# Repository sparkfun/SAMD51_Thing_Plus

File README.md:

SparkFun SAMD51 Thing Plus
========================================

[*SparkFun SAMD51 Thing Plus (DEV-14713)*](https://www.sparkfun.com/products/14713)

With a 32-bit ARM Cortex-M4F MCU, the [SAMD51 Thing Plus](https://www.sparkfun.com/products/14713) is one of our most powerful microcontroller boards yet! The SAMD51 Thing Plus provides you with an economical and easy to use development platform if you're needing more power with minimal working space. This Thing even comes flashed with the same convenient UF2 bootloader as the RedBoard Turbo. To make the Thing Plus even easier to use, we've moved a few pins around to make the board Feather compatible and it utilizes our handy Qwiic Connect System which means no soldering or shields are required to connect it to the rest of your system!

The ATSAMD51J20 utilizes a 32-bit ARM Cortex-M4 processor with Floating Point Unit (FPU), running up to 120MHz, up to 1MB of flash memory, up to 256KB of SRAM with ECC, up to 6 SERCOM interfaces, and other features. In addition to the USB interface and Qwiic connection, a The SAMD51 Thing Plus provides a 600mA 3.3V regulator and LiPo charger.

Repository Contents
-------------------

* **/Documentation** - Documentation (datasheet, graphical datasheet, etc.)
* **/Hardware** - Eagle design files (.brd, .sch)
* **/Production** - Production panel files (.brd)

Documentation
--------------
* [**Hookup Guide**](https://learn.sparkfun.com/tutorials/samd51-thing-plus-hookup-guide) - Basic hookup guide for the SAMD51 Thing Plus.
* [**SAMD51 Datasheet**](https://github.com/sparkfun/SAMD51_Thing_Plus/blob/master/Documents/SAMD51_datasheet.pdf)- Datasheet for the SAMD51 chip.
* [**Graphical Datasheet**](https://github.com/sparkfun/SAMD51_Thing_Plus/blob/master/Documents/SAMD51_Thing_Plus_graphical_datasheet_v01-02.pdf)- Graphical datasheet for the SAMD51 Thing Plus.

Product Versions
----------------
* [DEV-14713](https://www.sparkfun.com/products/14713) - Initial release of the SAMD51 Thing Plus.

Version History
---------------
* [V_1.0](https://github.com/sparkfun/SAMD51_Thing_Plus/releases/tag/v1.0.0) - Initial release of the SAMD51 Thing Plus.

License Information
-------------------

This product is _**open source**_! 

Please review the LICENSE.md file for license information.

If you have any questions or concerns on licensing, please visit the [SparkFun Forum](https://forum.sparkfun.com/index.php) and post a topic.

Distributed as-is; no warranty is given.

- Your friends at SparkFun.

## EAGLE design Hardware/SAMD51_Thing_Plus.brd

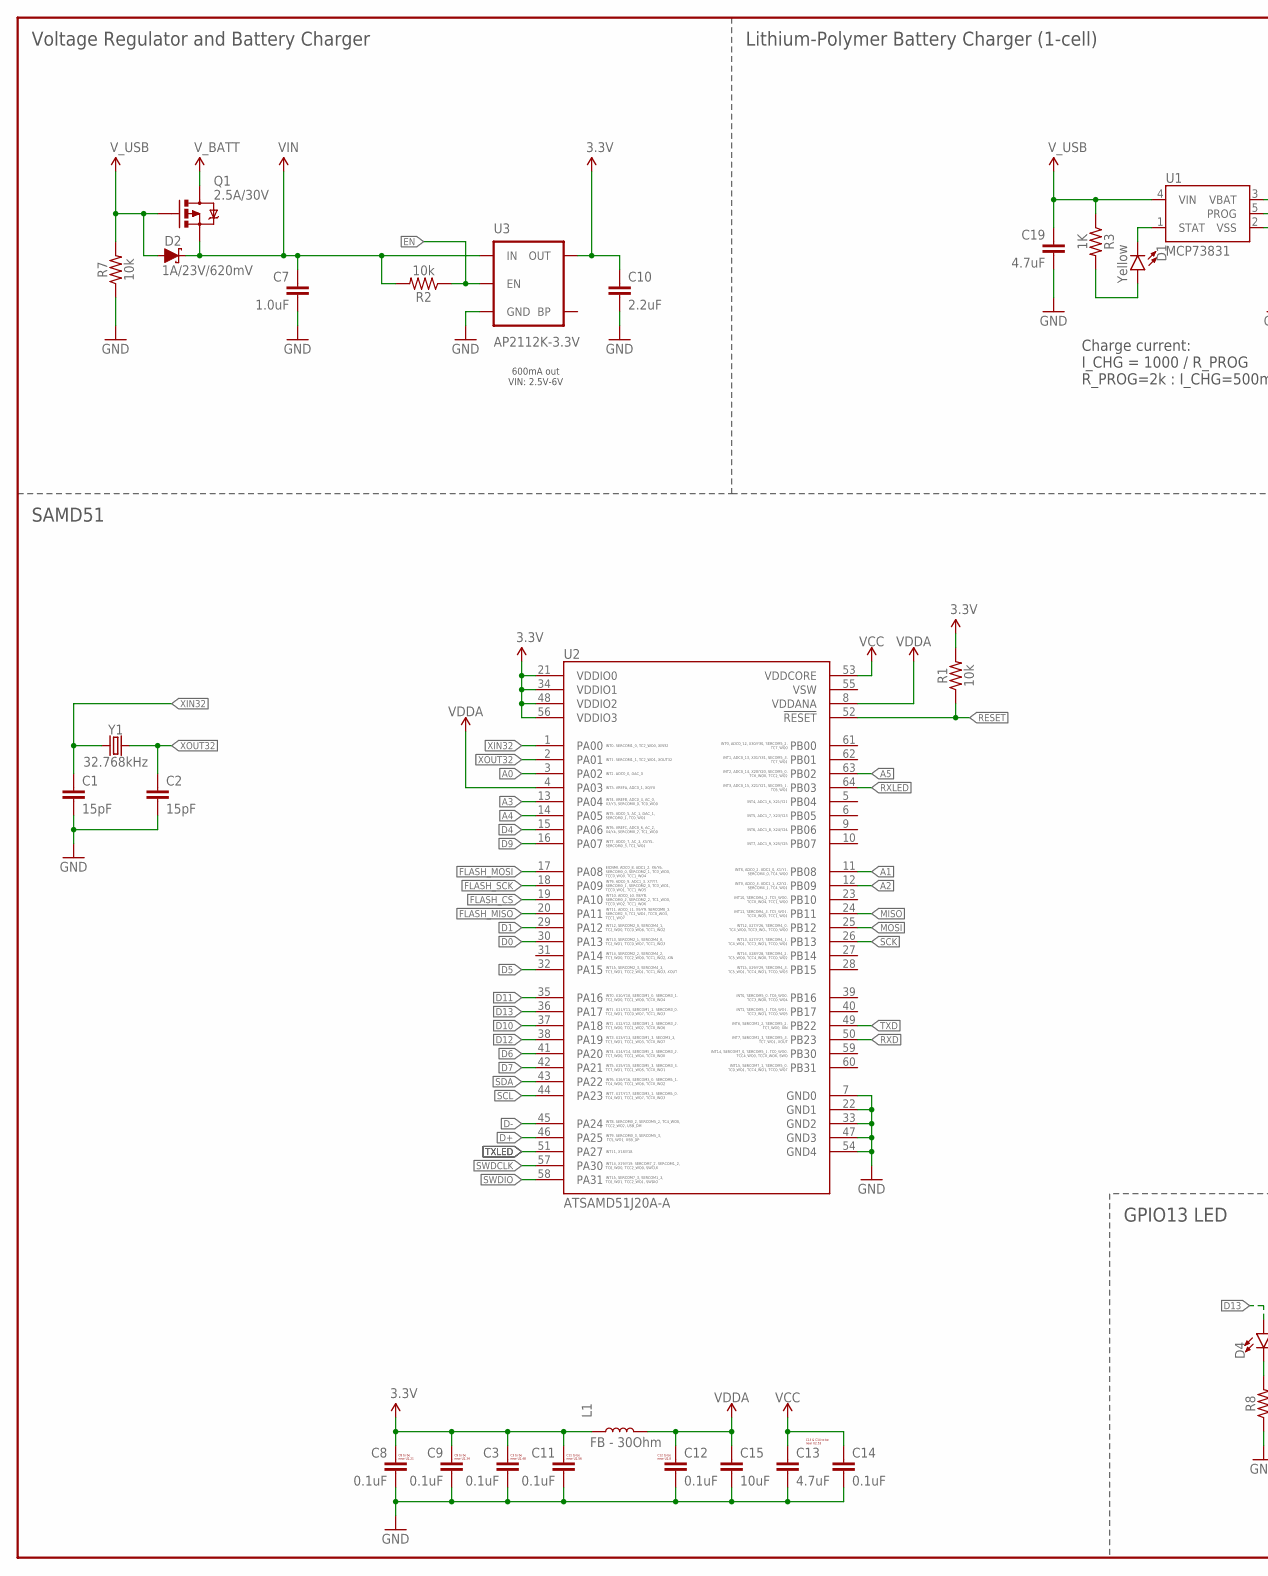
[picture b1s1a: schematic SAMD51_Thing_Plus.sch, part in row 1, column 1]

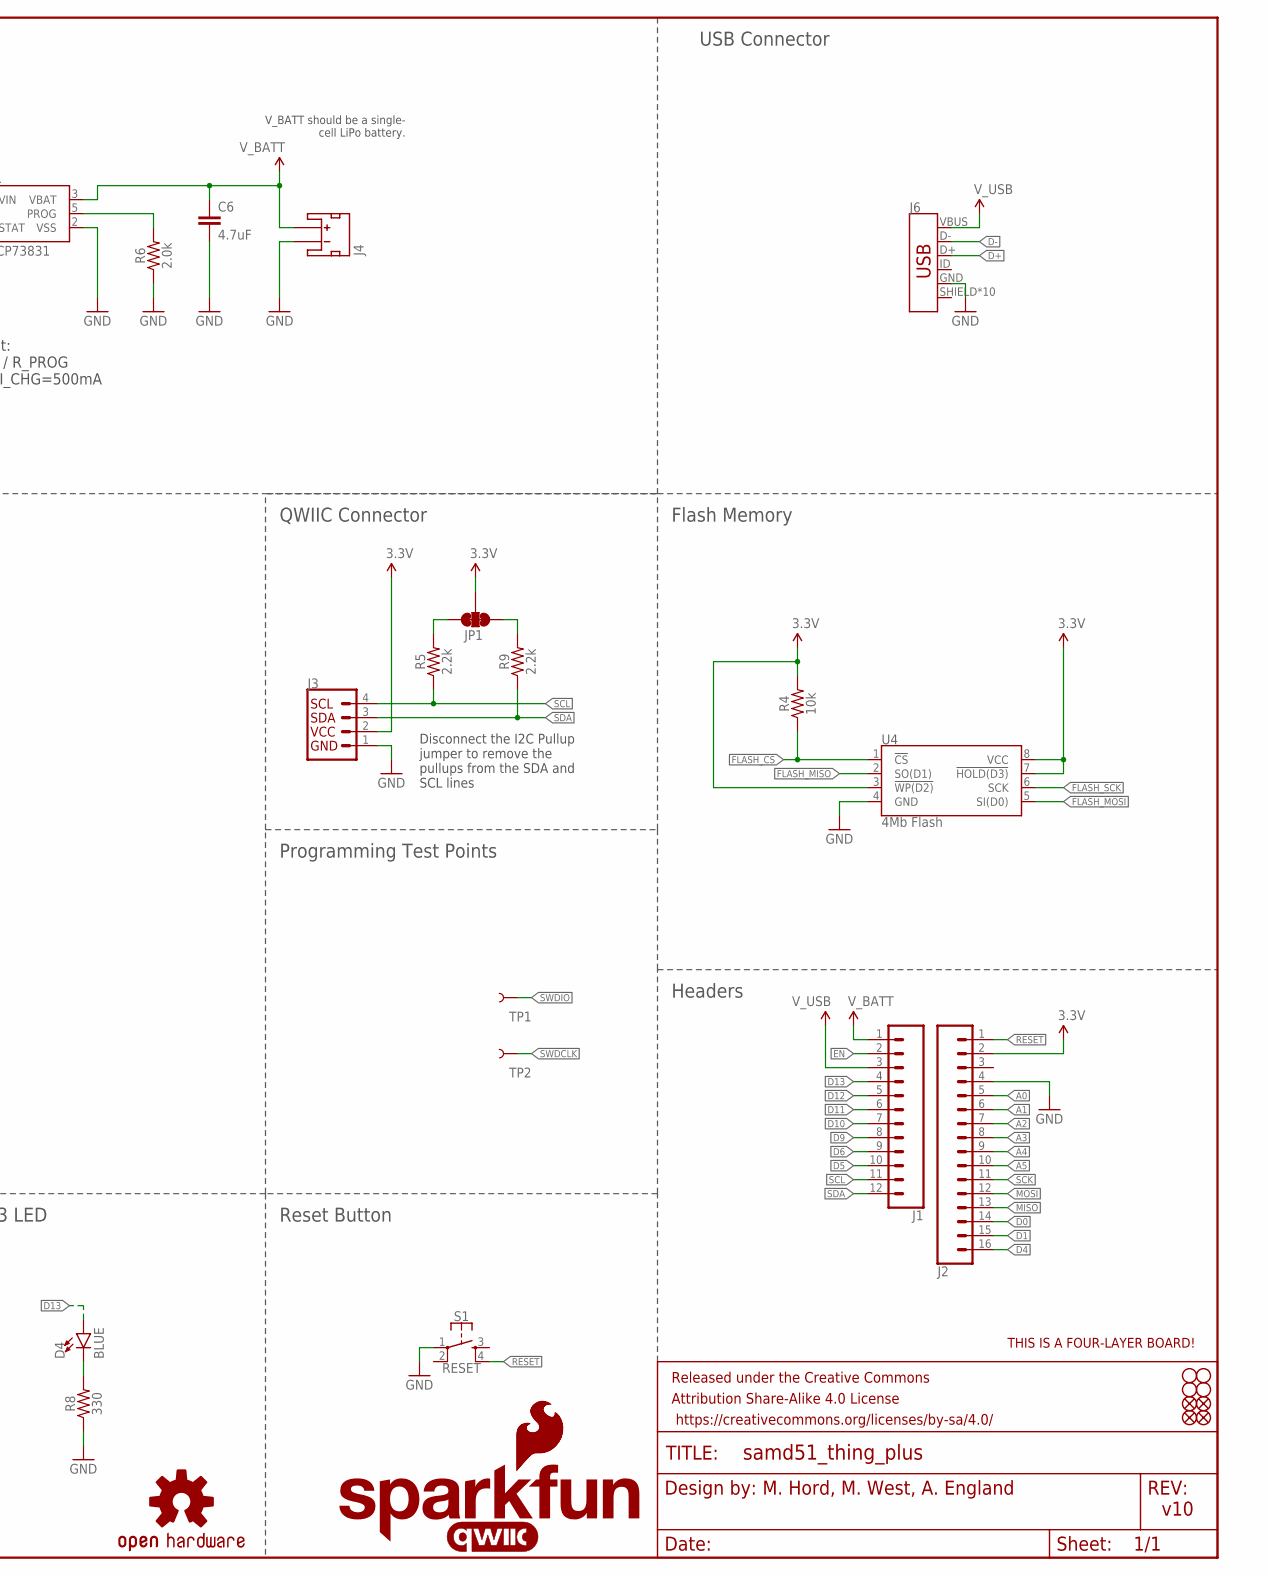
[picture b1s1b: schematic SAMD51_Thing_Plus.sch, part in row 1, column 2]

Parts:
C1, C2: 15pF; 0402
C3, C8, C9, C11, C12, C14: 0.1uF; 0402
C6, C13, C19: 4.7uF; 0603
C7: 1.0uF; 0603
C10: 2.2uF; 0603
C15: 10uF; 0805
D1: Yellow; LED-0603
D2: 1A/23V/620mV; SOD-323
D4: BLUE; LED-0603
FD1, FD2, FD3, FD4: FIDUCIALUFIDUCIAL; FIDUCIAL-MICRO
FRAME1: FRAME-LEDGER; CREATIVE_COMMONS
H1, H2, H3, H4: STAND-OFF
J1: CONN_12SM_SQ_NO_SILK; 1X12_SM_SQ_NOSILK
J2: CONN_161X16_SM_SQ_NOSILK; 1X16_SM_SQ_NOSILK
J3: QWIIC_CONNECTORJS-1MM; JST04_1MM_RA
J4: JST_2MM_MALE; JST-2-SMD
J6: AMP FCI 10103594-0001LF; USB-MICROB-PTH-MILL
JP1: JUMPER-SMT_3_2-NC_TRACE_SILK; SMT-JUMPER_3_2-NC_TRACE_SILK
L1: FB - 30Ohm; 0603
LOGO1: FOUR_LAYER_WARNING
LOGO2: OSHW-LOGOMINI; OSHW-LOGO-MINI
LOGO3: SFE_LOGO_NAME_FLAME.1_INCH; SFE_LOGO_NAME_FLAME_.1
LOGO4: SFE_LOGO_FLAME.1_INCH; SFE_LOGO_FLAME_.1
Q1: 2.5A/30V; SOT23-3@1
R1, R2, R4, R7: 10k; 0603
R3: 1K; 0603
R5, R9: 2.2k; 0603
R6: 2.0k; 0603
R8: 330; 0603
S1: RESET; TACTILE_SWITCH_SMD_4.6X2.8MM
TP1, TP2: TEST-POINTTP_15TH_THRU; TP_15TH
U1: MCP73831; SOT23-5
U2: ATSAMD51J20A-A; TQFP64
U3: AP2112K-3.3V; SOT23-5
U4: 4Mb Flash; SO08
U$69: QWIIC_LOGO_5MM; QWIIC_5MM
Y1: 32.768kHz; CRYSTAL-SMD-3.2X1.5MM

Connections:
3.3V: C3.1, C8.1, C9.1, C10.1, C11.1, J2.2, J3.2, JP1.2, L1.1, R1.2, R4.2, U2.21 (VDDIO0), U2.34 (VDDIO1), U2.48 (VDDIO2), U2.56 (VDDIO3), U3.5 (OUT), U4.3 (!WP(D2)), U4.7 (!HOLD(D3)), U4.8 (VCC)
!RESET: J2.1, R1.1, S1.4, U2.52 (!RESET)
A0: J2.5, U2.3 (PA02)
A1: J2.6, U2.11 (PB08)
A2: J2.7, U2.12 (PB09)
A3: J2.8, U2.13 (PA04)
A4: J2.9, U2.14 (PA05)
A5: J2.10, U2.63 (PB02)
D0: J2.14, U2.30 (PA13)
D1: J2.15, U2.29 (PA12)
D4: J2.16, U2.15 (PA06)
D5: J1.10, U2.32 (PA15)
D6: J1.9, U2.41 (PA20)
D7: U2.42 (PA21)
D9: J1.8, U2.16 (PA07)
D10: J1.7, U2.37 (PA18)
D11: J1.6, U2.35 (PA16)
D12: J1.5, U2.38 (PA19)
D13: D4.A, J1.4, U2.36 (PA17)
D+: J6.D+, U2.46 (PA25)
D-: J6.D-, U2.45 (PA24)
EN: J1.2, R2.1, U3.3 (EN)
FLASH_CS: R4.1, U2.19 (PA10), U4.1 (!CS)
FLASH_MISO: U2.20 (PA11), U4.2 (SO(D1))
FLASH_MOSI: U2.17 (PA08), U4.5 (SI(D0))
FLASH_SCK: U2.18 (PA09), U4.6 (SCK)
GND: C1.2, C2.2, C3.2, C6.2, C7.2, C8.2, C9.2, C10.2, C11.2, C12.2, C13.2, C14.2, C15.2, C19.2, J2.4, J3.1, J4.1 (-), J6.GND, R6.1, R7.1, R8.1, S1.1, U1.2 (VSS), U2.7 (GND0), U2.22 (GND1), U2.33 (GND2), U2.47 (GND3), U2.54 (GND4), U3.2 (GND), U4.4 (GND)
MISO: J2.13, U2.24 (PB11)
MOSI: J2.12, U2.25 (PB12)
unnamed: D4.C, R8.2
unnamed: JP1.3, R5.2
unnamed: JP1.1, R9.2
unnamed: D1.C, U1.1 (STAT)
unnamed: R6.2, U1.5 (PROG)
unnamed: D1.A, R3.2
RXD: U2.50 (PB23)
RXLED: U2.64 (PB03)
SCK: J2.11, U2.26 (PB13)
SCL: J1.11, J3.4, R5.1, U2.44 (PA23)
SDA: J1.12, J3.3, R9.1, U2.43 (PA22)
SWDCLK: TP2.P$1, U2.57 (PA30)
SWDIO: TP1.P$1, U2.58 (PA31)
TXD: U2.49 (PB22)
TXLED: U2.51 (PA27)
VCC: C13.1, C14.1, U2.53 (VDDCORE)
VDDA: C12.1, C15.1, L1.2, U2.4 (PA03), U2.8 (VDDANA)
VIN: C7.1, D2.C, Q1.2 (S), R2.2, U3.1 (IN)
V_BATT: C6.1, J1.1, J4.2 (+), Q1.3 (D), U1.3 (VBAT)
V_USB: C19.1, D2.A, J1.3, J6.VBUS, Q1.1 (G), R3.1, R7.2, U1.4 (VIN)
XIN32: C1.1, U2.1 (PA00), Y1.P$1 (1)
XOUT32: C2.1, U2.2 (PA01), Y1.P$2 (2)

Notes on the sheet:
V_BATT should be a single- cell LiPo battery.
Charge current: I_CHG = 1000 / R_PROG R_PROG=2k : I_CHG=500mA
Voltage Regulator and Battery Charger
Lithium-Polymer Battery Charger (1-cell)
600mA out VIN: 2.5V-6V
Reset Button
GPIO13 LED
Headers
v10
C8 to be near U2.21
C9 to be near U2.34
C3 to be near U2.48
C11 to be near U2.56
C12 to be near U2.8
C13 & C14 to be near U2.53
QWIIC Connector
SAMD51
USB Connector
M. Hord, M. West, A. England
Programming Test Points
Flash Memory
Disconnect the I2C Pullup jumper to remove the pullups from the SDA and SCL lines

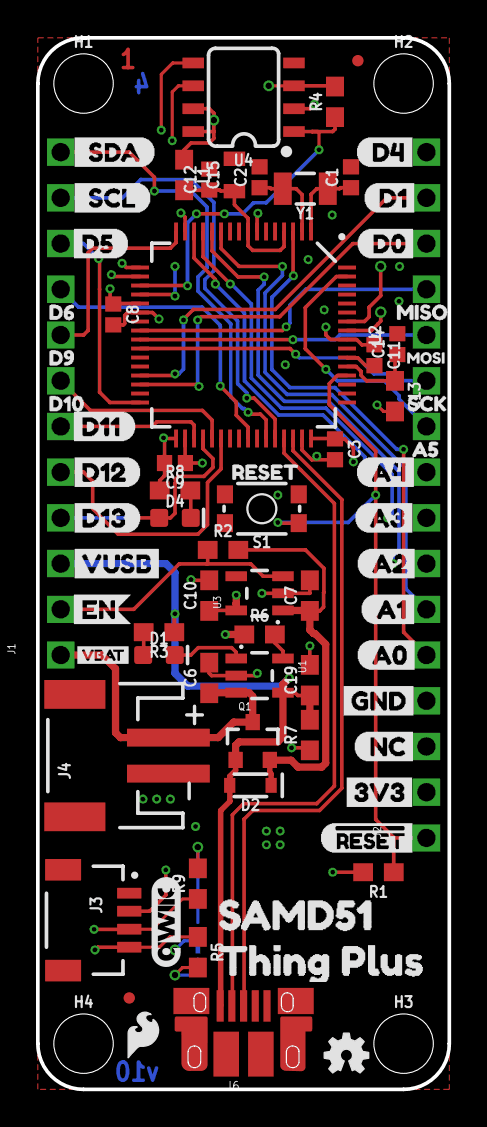
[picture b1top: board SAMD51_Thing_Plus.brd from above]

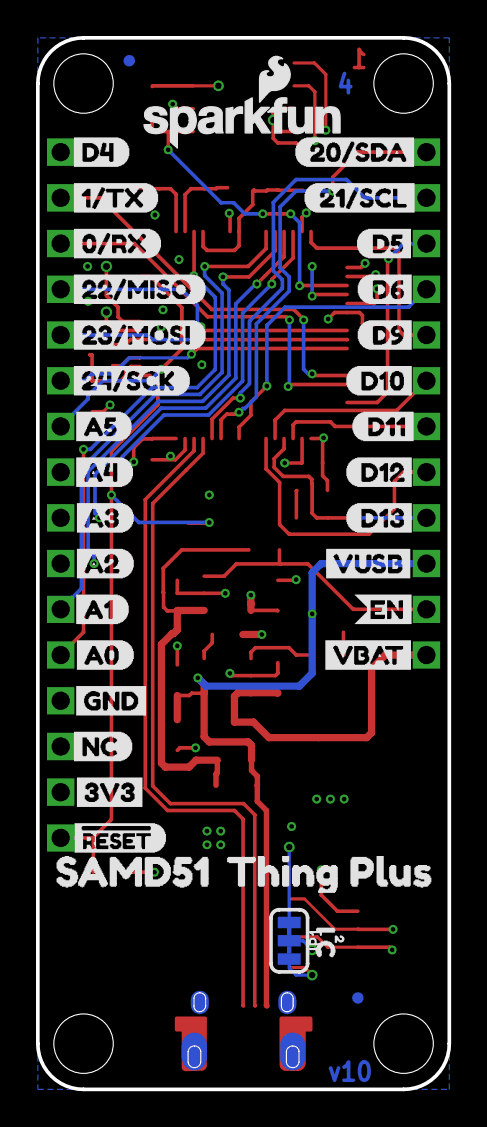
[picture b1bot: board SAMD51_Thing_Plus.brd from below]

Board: 4 copper layers, 22.9 x 58.4 mm, 120 parts (36 on the bottom side), 46 nets.

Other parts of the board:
U$4: RESET27
U$5: #RESET15
U$6: #RESET0
U$7: 3V32
U$8: A04
U$9: A15
U$10: A26
U$11: A37
U$12: A48
U$13: A523
U$14: SCK24
U$15: 3V33
U$16: MISO26
U$17: D09
U$18: D110
U$19: D411
U$20: GND3
U$21: GND0
U$22: EN0
U$23: VUSB2
U$24: D1312
U$25: D120
U$26: D1113
U$27: A014
U$28: A113
U$29: D515
U$30: _SCL16
U$31: ORDERING_INSTRUCTIONS
U$32: _SDA17
U$33: D63
U$34: D92
U$35: MOSI0
U$36: VBAT1
U$37: A212
U$38: A311
U$39: A410
U$40: A59
U$41: 21#SCL1
U$42: 22#MISO4
U$43: 23#MOSI3
U$44: 1#TX1
U$46: D41
U$47: 24#SCK2
U$48: 0#RX0
U$49: D518
U$50: D619
U$51: D920
U$52: D1122
U$53: D1021
U$54: D1223
U$55: D1324
U$56: VUSB1
U$57: EN25
U$58: VBAT2
U$59: D100
U$60: NC0
U$61: NC1
U$62: 20#SDA0
U$63, U$65: SAMD510
U$64, U$66: THING_PLUS1
U$67: I_C0
U$68: 21

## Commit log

2018-04-19 First commit for samd51
2018-04-25 Post review feedback and engineer checklist
2018-04-25 Fixes from QC review
2018-04-25 Replaced retired 1.0uF cap with new one
2018-06-01 Original thing plus
2018-06-04 Buzzard Text
2018-06-05 Add flash, buzzard labels
2018-06-05 Changes from review
2018-06-06 A few more changes to text labels on schematic
2018-06-06 Changes from QC review
2018-06-26 Convert labels to Fredoka, headers to smaller square pads
2018-06-29 Fix SPI pinout for flash and header
2018-06-29 Clear some errors
2018-07-06 Moving QWIIC connector, adding board name, moving bottom-placed capacitor to top
2018-07-23 updating version number
2019-01-15 connecting D4 to match feather footprint, removing short on USB connector
2019-01-16 post checklist changes
2019-01-16 adding i2c labels from double check
2019-04-12 pre-design review changes
2019-04-18 engineer run of checklist-REDS
2019-04-19 post qc checklist
2019-05-24 Update product image and link
2019-05-24 Update to correct information
    Updated from ESP32 information
2019-06-17 Correct Label in Schematic
    - The Dev board was incorrectly labeled as 4MB in the schematic. It is technically 4Mb after checking the BOM.
2019-08-05 Adding documentation
    Adding documentation as backup for Sparkle
2019-08-05 Update
    Modifications for added documentation
2019-09-12 Forum topic removed
2021-08-02 updated documentation
    Fixed sercom and interrupt values on pin 13/LED
2021-08-02 Update README.md
    update graphical datasheet link
2021-08-02 Add files via upload
    Fix sercom error
2021-08-02 Delete SAMD51_Thing_Plus_graphical_datasheet_v01-01.pdf
    delete file
2021-08-02 Fix sercom values
    update sercom values
2021-10-05 Add original bootloader binaries
    Add the original Sparkfan SAMD51 Thing Plus bootloader binaries to the
    Thing Plus repo to keep more pieces of the product together.
    These files were copied from
    https://github.com/sparkfun/Arduino_Boards/commit/921656dcec4a28d10c3ff9c6128fa23f269c7568
2021-10-06 Fix automatic reset into bootloader
    The Arduino automatic flashing mechanism triggers a reboot into the
    bootloader by setting the UART to 1200 baud and then closing the
    connection. The Arduino framework code running on the microcontroller
    detects this change, sets a magic value in the last four bytes of SRAM
    and resets. The bootloader checks for this magic value and remains in
    the bootloader if it's present, otherwise it jumps to the application
2021-10-06 Add uf2-samdx1 board config and updated bootloader
    Since the board config used to build the original bootloader appears
    to have been lost, this commit includes a reconstructed board config.
    Importantly, this board config also corrects the microcontroller model
    to SAMD51J20A.
    VENDOR_NAME was copied from the SAMD51 MicroMod board config.
    INDEX_URL links to the SAMD51 Thing Plus product page.
2023-05-02 Update graphical datasheet
    Fixes pin labels for RX/TX (swapped)

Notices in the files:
parts and their libraries:
SparkFun-Resistors: Licensing: Creative Commons ShareAlike 4.0 International - https://creativecommons.org/licenses/by-sa/4.0
SparkFun-Aesthetics: Released under the Creative Commons Attribution Share-Alike 4.0 License
SparkFun-Aesthetics: https://creativecommons.org/licenses/by-sa/4.0
